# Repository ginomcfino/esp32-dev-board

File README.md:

# ESP32-S3 Development Board

An ESP32-S3 development board design combining USB-C connectivity, 3.3 V regulation, battery charging and fuel monitoring, GPIO headers, and an I2C interface.

**Status:** CAD design study; not yet fabricated or bench-tested. ERC, DRC, and schematic-to-board checks report zero findings in KiCad 10.0.5 under the saved project rules. Open circuit items are recorded in the check notes.

This is my manually developed circuit and PCB design. Component libraries, manufacturer models, and other supplied assets retain their original attribution.

- [Hardware source](hardware/): schematic, PCB, and project settings.
- [Schematic PDF](exports/schematic.pdf) and [component list](exports/bom.csv).
- [Visual guide](docs/README.md): labeled board and schematic views.
- [Check notes](docs/checks/README.md): automated-check results and circuit review findings.

Open `hardware/esp32-s3-development-board.kicad_pro` with KiCad 10 and its standard symbol, footprint, and 3D model libraries.

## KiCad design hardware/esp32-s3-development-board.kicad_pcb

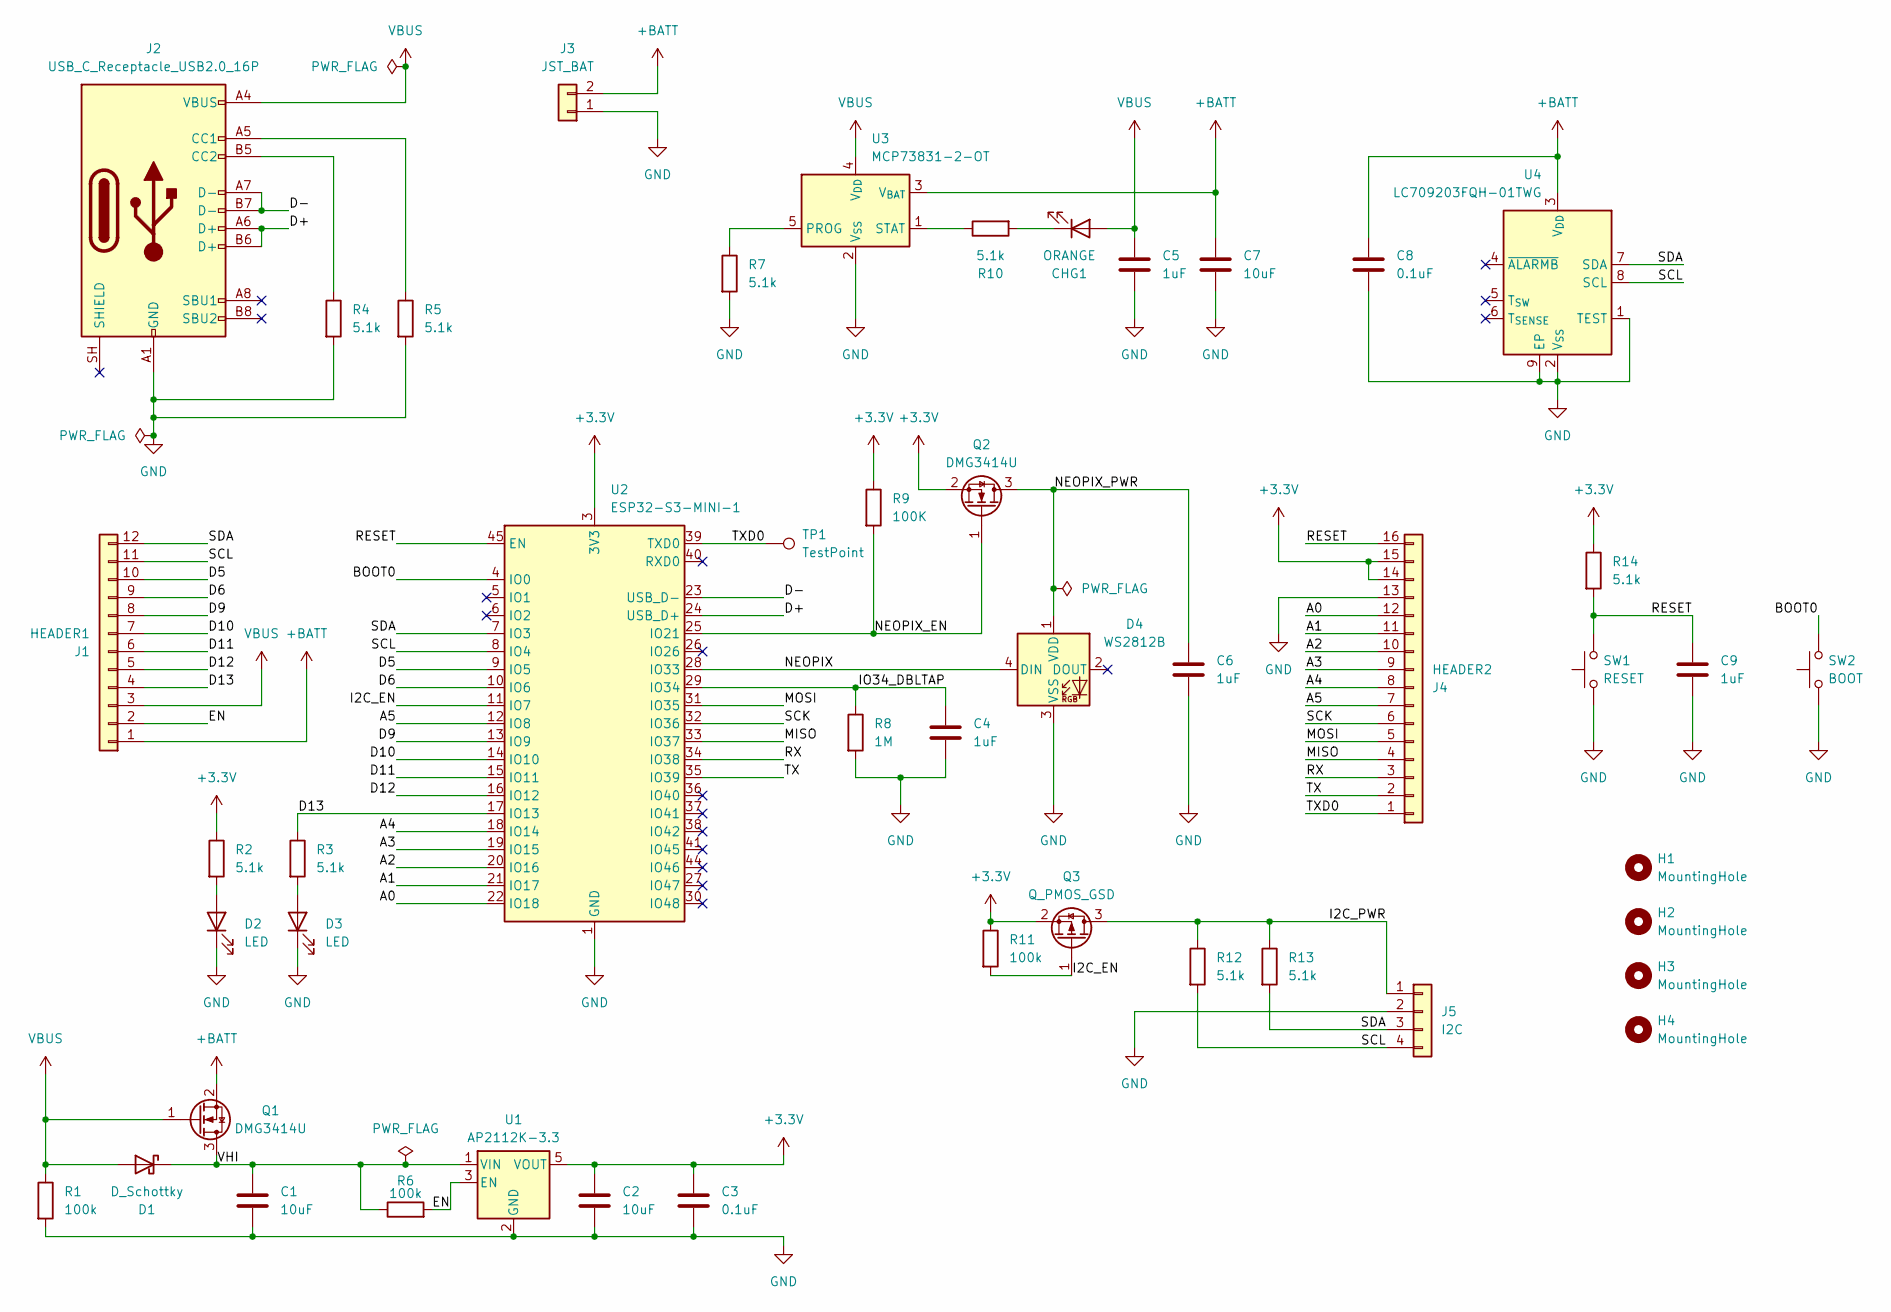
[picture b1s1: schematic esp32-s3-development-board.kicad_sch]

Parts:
C1, C2, C7: 10uF; C_0603_1608Metric
C3, C8: 0.1uF; C_0402_1005Metric
C4, C5, C6, C9: 1uF; C_0402_1005Metric
CHG1: ORANGE; LED_0603_1608Metric
D1: D_Schottky; D_SOD-323
D2, D3: LED; LED_0603_1608Metric
D4: WS2812B; LED_WS2812B-2020_PLCC4_2.0x2.0mm
H1, H2: MountingHole; MountingHole_2.2mm_M2
H3, H4: MountingHole; MountingHole_2.2mm_M2_Pad
J1: HEADER1; PinHeader_1x12_P2.54mm_Vertical
J2: USB_C_Receptacle_USB2.0_16P; USB_C_Receptacle_GCT_USB4105-xx-A_16P_TopMnt_Horizontal
J3: JST_BAT; JST_SH_SM02B-SRSS-TB_1x02-1MP_P1.00mm_Horizontal
J4: HEADER2; PinHeader_1x16_P2.54mm_Vertical
J5: I2C; JST_SH_BM04B-SRSS-TB_1x04-1MP_P1.00mm_Vertical
Q1, Q2: DMG3414U; SOT-23
Q3: Q_PMOS_GSD; SOT-23
R1, R6, R11: 100k; R_0402_1005Metric
R2, R3, R4, R5, R7, R10, R12, R13, R14: 5.1k; R_0402_1005Metric
R8: 1M; R_0402_1005Metric
R9: 100K; R_0402_1005Metric
SW1: RESET; SW_SPST_PTS810
SW2: BOOT; SW_SPST_PTS810
TP1: TestPoint; TestPoint_Pad_D1.0mm
U1: AP2112K-3.3; SOT-23-5
U2: ESP32-S3-MINI-1; ESP32-S2-MINI-1
U3: MCP73831-2-OT; SOT-23-5
U4: LC709203FQH-01TWG; WDFN-8-1EP_4x3mm_P0.65mm_EP2.4x1.8mm

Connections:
+3.3V: C2.1, C3.1, J4.14, J4.15, Q2.2 (S), Q3.2 (S), R2.1, R9.1, R11.1, R14.1, U1.5 (VOUT), U2.3 (3V3)
+BATT: C7.1, C8.1, J1.1, J3.2, Q1.2 (S), U3.3 (V_{BAT}), U4.3 (V_{DD})
/A0: J4.12, U2.22 (IO18)
/A1: J4.11, U2.21 (IO17)
/A2: J4.10, U2.20 (IO16)
/A3: J4.9, U2.19 (IO15)
/A4: J4.8, U2.18 (IO14)
/A5: J4.7, U2.12 (IO8)
/BOOT0: SW2.2, U2.4 (IO0)
/D5: J1.10, U2.9 (IO5)
/D6: J1.9, U2.10 (IO6)
/D9: J1.8, U2.13 (IO9)
/D10: J1.7, U2.14 (IO10)
/D11: J1.6, U2.15 (IO11)
/D12: J1.5, U2.16 (IO12)
/D13: J1.4, R3.1, U2.17 (IO13)
/D+: J2.A6 (D+), J2.B6 (D+), U2.24 (USB_D+)
/D-: J2.A7 (D-), J2.B7 (D-), U2.23 (USB_D-)
/EN: J1.2, R6.2, U1.3 (EN)
/I2C_EN: Q3.1 (G), R11.2, U2.11 (IO7)
/I2C_PWR: J5.1, Q3.3 (D), R12.1, R13.1
/IO34_DBLTAP: C4.1, R8.1, U2.29 (IO34)
/MISO: J4.4, U2.33 (IO37)
/MOSI: J4.5, U2.31 (IO35)
/NEOPIX: D4.4 (DIN), U2.28 (IO33)
/NEOPIX_EN: Q2.1 (G), R9.2, U2.25 (IO21)
/NEOPIX_PWR: C6.1, D4.1 (VDD), Q2.3 (D)
/RESET: C9.1, J4.16, R14.2, SW1.2, U2.45 (EN)
/RX: J4.3, U2.34 (IO38)
/SCK: J4.6, U2.32 (IO36)
/SCL: J1.11, J5.4, R12.2, U2.8 (IO4), U4.8 (SCL)
/SDA: J1.12, J5.3, R13.2, U2.7 (IO3), U4.7 (SDA)
/TX: J4.2, U2.35 (IO39)
/TXD0: J4.1, TP1.1 (1_1), U2.39 (TXD0)
/VHI: C1.1, D1.1 (K), Q1.3 (D), R6.1, U1.1 (VIN)
GND: C1.2, C2.2, C3.2, C4.2, C5.2, C6.2, C7.2, C8.2, C9.2, D2.1 (K), D3.1 (K), D4.3 (VSS), J2.A1 (GND), J2.A12 (GND), J2.B1 (GND), J2.B12 (GND), J3.1, J4.13, J5.2, R1.2, R4.2, R5.2, R7.2, R8.2, SW1.1, SW2.1, U1.2 (GND), U2.1 (GND), U2.2 (GND), U2.42 (GND), U2.43 (GND), U2.46 (GND), U2.47 (GND), U2.48 (GND), U2.49 (GND), U2.50 (GND), U2.51 (GND), U2.52 (GND), U2.53 (GND), U2.54 (GND), U2.55 (GND), U2.56 (GND), U2.57 (GND), U2.58 (GND), U2.59 (GND), U2.60 (GND), U2.61 (GND), U2.62 (GND), U2.63 (GND), U2.64 (GND), U2.65 (GND), U3.2 (V_{SS}), U4.1 (TEST), U4.2 (V_{SS}), U4.9 (EP)
unnamed: CHG1.1 (K), R10.2
unnamed: D2.2 (A), R2.2
unnamed: D3.2 (A), R3.2
unnamed: J2.A5 (CC1), R5.1
unnamed: J2.B5 (CC2), R4.1
unnamed: R7.1, U3.5 (PROG)
unnamed: R10.1, U3.1 (STAT)
VBUS: C5.1, CHG1.2 (A), D1.2 (A), J1.3, J2.A4 (VBUS), J2.A9 (VBUS), J2.B4 (VBUS), J2.B9 (VBUS), Q1.1 (G), R1.1, U3.4 (V_{DD})

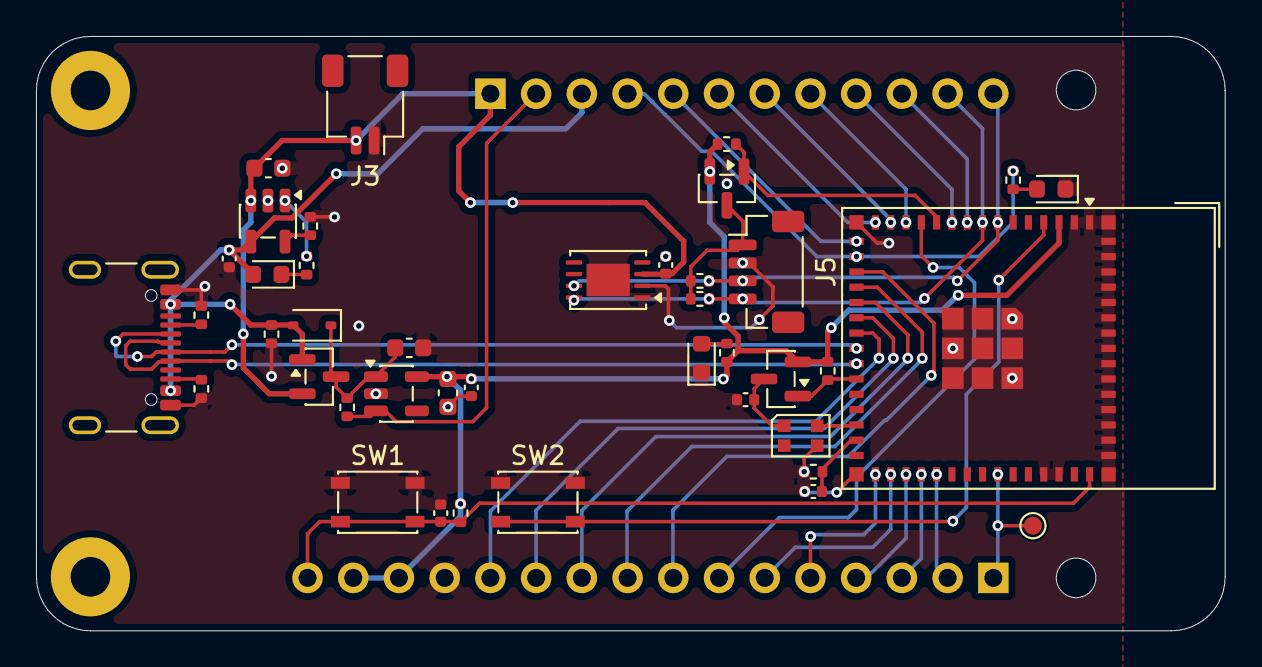
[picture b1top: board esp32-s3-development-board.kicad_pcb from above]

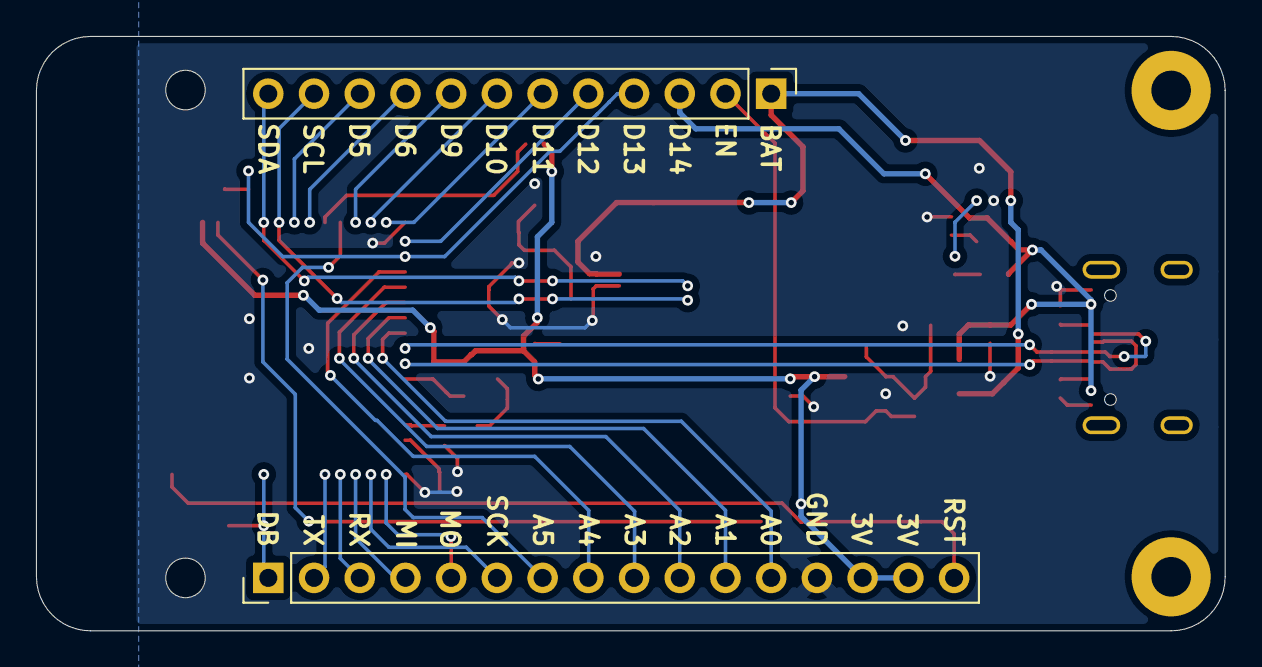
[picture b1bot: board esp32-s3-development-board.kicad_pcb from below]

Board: 2 copper layers, 66.0 x 33.0 mm, 47 parts (2 on the bottom side), 44 nets.

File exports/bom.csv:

"Refs","Value","Footprint","Qty","DNP"
"C1","10uF","Capacitor_SMD:C_0603_1608Metric","1",""
"C2","10uF","Capacitor_SMD:C_0603_1608Metric","1",""
"C3","0.1uF","Capacitor_SMD:C_0402_1005Metric","1",""
"C4","1uF","Capacitor_SMD:C_0402_1005Metric","1",""
"C5","1uF","Capacitor_SMD:C_0402_1005Metric","1",""
"C6","1uF","Capacitor_SMD:C_0402_1005Metric","1",""
"C7","10uF","Capacitor_SMD:C_0603_1608Metric","1",""
"C8","0.1uF","Capacitor_SMD:C_0402_1005Metric","1",""
"C9","1uF","Capacitor_SMD:C_0402_1005Metric","1",""
"CHG1","ORANGE","LED_SMD:LED_0603_1608Metric","1",""
"D1","D_Schottky","Diode_SMD:D_SOD-323","1",""
"D2","LED","LED_SMD:LED_0603_1608Metric","1",""
"D3","LED","LED_SMD:LED_0603_1608Metric","1",""
"D4","WS2812B","LED_SMD:LED_WS2812B-2020_PLCC4_2.0x2.0mm","1",""
"J1","HEADER1","Connector_PinHeader_2.54mm:PinHeader_1x12_P2.54mm_Vertical","1",""
"J2","USB_C_Receptacle_USB2.0_16P","Connector_USB:USB_C_Receptacle_GCT_USB4105-xx-A_16P_TopMnt_Horizontal","1",""
"J3","JST_BAT","Connector_JST:JST_SH_SM02B-SRSS-TB_1x02-1MP_P1.00mm_Horizontal","1",""
"J4","HEADER2","Connector_PinHeader_2.54mm:PinHeader_1x16_P2.54mm_Vertical","1",""
"J5","I2C","Connector_JST:JST_SH_BM04B-SRSS-TB_1x04-1MP_P1.00mm_Vertical","1",""
"Q1","DMG3414U","Package_TO_SOT_SMD:SOT-23","1",""
"Q2","DMG3414U","Package_TO_SOT_SMD:SOT-23","1",""
"Q3","Q_PMOS_GSD","Package_TO_SOT_SMD:SOT-23","1",""
"R1","100k","Resistor_SMD:R_0402_1005Metric","1",""
"R2","5.1k","Resistor_SMD:R_0402_1005Metric","1",""
"R3","5.1k","Resistor_SMD:R_0402_1005Metric","1",""
"R4","5.1k","Resistor_SMD:R_0402_1005Metric","1",""
"R5","5.1k","Resistor_SMD:R_0402_1005Metric","1",""
"R6","100k","Resistor_SMD:R_0402_1005Metric","1",""
"R7","5.1k","Resistor_SMD:R_0402_1005Metric","1",""
"R8","1M","Resistor_SMD:R_0402_1005Metric","1",""
"R9","100K","Resistor_SMD:R_0402_1005Metric","1",""
"R10","5.1k","Resistor_SMD:R_0402_1005Metric","1",""
"R11","100k","Resistor_SMD:R_0402_1005Metric","1",""
"R12","5.1k","Resistor_SMD:R_0402_1005Metric","1",""
"R13","5.1k","Resistor_SMD:R_0402_1005Metric","1",""
"R14","5.1k","Resistor_SMD:R_0402_1005Metric","1",""
"SW1","RESET","Button_Switch_SMD:SW_SPST_PTS810","1",""
"SW2","BOOT","Button_Switch_SMD:SW_SPST_PTS810","1",""
"TP1","TestPoint","TestPoint:TestPoint_Pad_D1.0mm","1",""
"U1","AP2112K-3.3","Package_TO_SOT_SMD:SOT-23-5","1",""
"U2","ESP32-S3-MINI-1","RF_Module:ESP32-S2-MINI-1","1",""
"U3","MCP73831-2-OT","Package_TO_SOT_SMD:SOT-23-5","1",""
"U4","LC709203FQH-01TWG","Package_DFN_QFN:WDFN-8-1EP_4x3mm_P0.65mm_EP2.4x1.8mm","1",""
